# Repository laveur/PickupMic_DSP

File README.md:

# PickupMic_DSP
A Pickup Mic (Piezo) DSP Board

## Info
Based on a STM32F405 MCU, this allows you to connect up to four Piezo (Pickup Mics) To it and do some signal processing on it.

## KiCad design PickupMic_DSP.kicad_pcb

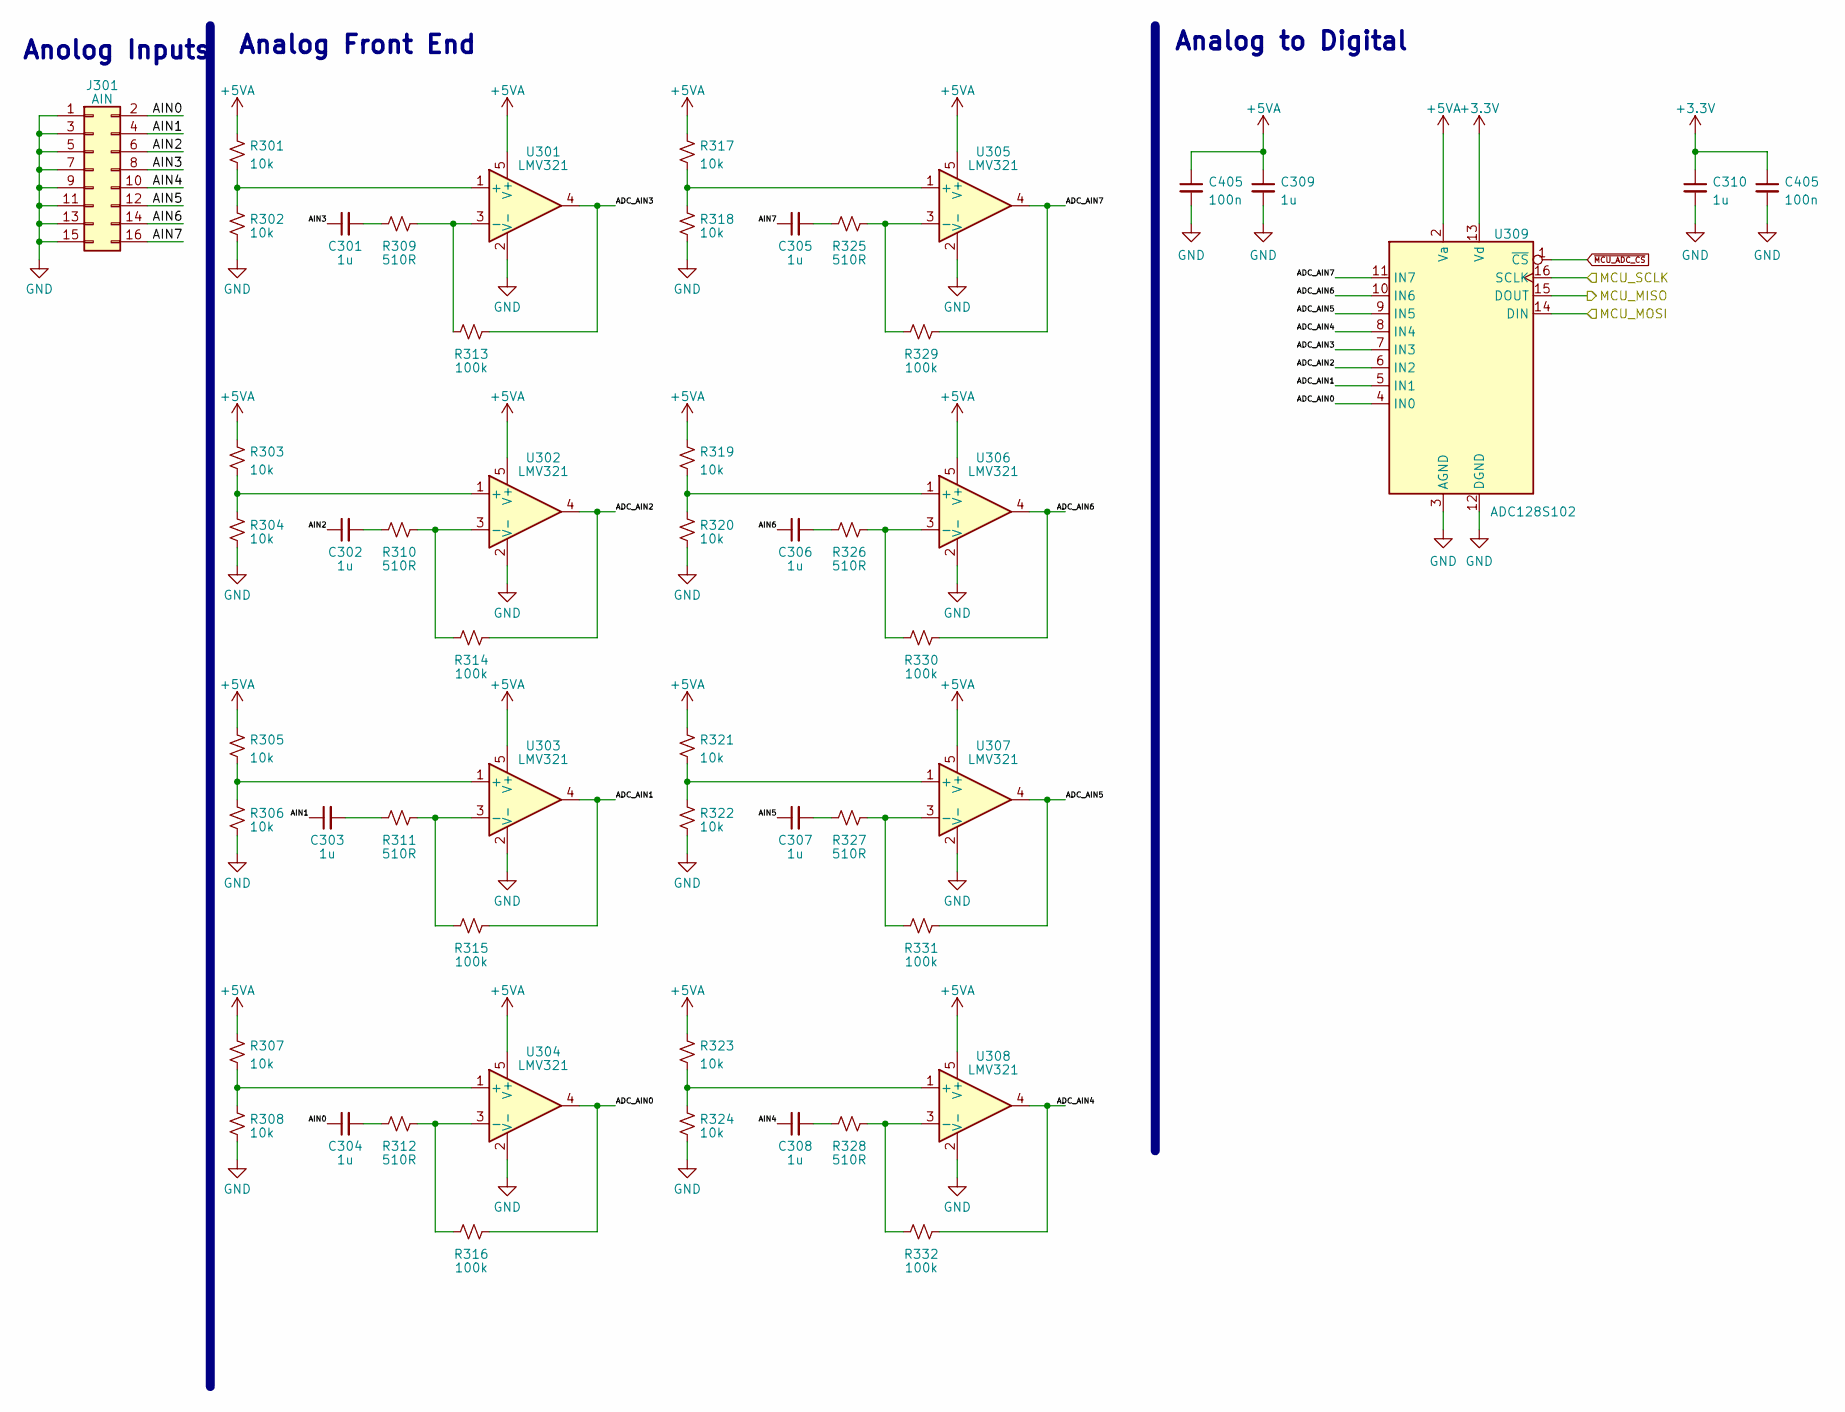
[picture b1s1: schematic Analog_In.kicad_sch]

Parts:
C301, C302, C303, C304, C305, C306, C307, C308, C309, C310: 1u; C_0402_1005Metric; LCSC C52923
C405: 100n; C_0402_1005Metric; LCSC C307331
J301: AIN; PinHeader_2x08_P2.54mm_Vertical
R301, R302, R303, R304, R305, R306, R307, R308, R317, R318, R319, R320, R321, R322, R323, R324: 10k; R_0402_1005Metric; LCSC C144807
R309, R310, R311, R312, R325, R326, R327, R328: 510R; R_0402_1005Metric; LCSC C25123
R313, R314, R315, R316, R329, R330, R331, R332: 100k; R_0402_1005Metric; LCSC C25086
U301, U302, U303, U304, U305, U306, U307, U308: LMV321; SOT-23-5; LCSC C7972
U309: ADC128S102; TSSOP-16_4.4x5mm_P0.65mm; LCSC C179666

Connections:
/Analog In/ADC_AIN0: R316.2, U304.4, U309.4 (IN0)
/Analog In/ADC_AIN1: R315.2, U303.4, U309.5 (IN1)
/Analog In/ADC_AIN2: R314.2, U302.4, U309.6 (IN2)
/Analog In/ADC_AIN4: R332.2, U308.4, U309.8 (IN4)
/Analog In/ADC_AIN5: R331.2, U307.4, U309.9 (IN5)
/Analog In/ADC_AIN6: R330.2, U306.4, U309.10 (IN6)
/Analog In/ADC_AIN7: R329.2, U305.4, U309.11 (IN7)
/Analog In/AIN0: C304.1, J301.2
/Analog In/AIN1: C303.1, J301.4
/Analog In/AIN2: C302.1, J301.6
/Analog In/AIN3: C301.1, J301.8
/Analog In/AIN4: C308.1, J301.10
/Analog In/AIN5: C307.1, J301.12
/Analog In/AIN6: C306.1, J301.14
/Analog In/AIN7: C305.1, J301.16
/Analog In/MCU_MISO: U309.15 (DOUT); also elsewhere on the board
/Analog In/MCU_MOSI: U309.14 (DIN); also elsewhere on the board
/Analog In/MCU_SCLK: U309.16 (SCLK); also elsewhere on the board
unnamed: C301.2, R309.2
unnamed: C302.2, R310.2
unnamed: C303.2, R311.2
unnamed: C304.2, R312.2
unnamed: C305.2, R325.2
unnamed: C306.2, R326.2
unnamed: C307.2, R327.2
unnamed: C308.2, R328.2
unnamed: R301.2, R302.2, U301.1 (+)
unnamed: R303.2, R304.1, U302.1 (+)
unnamed: R310.1, R314.1, U302.3 (-)
unnamed: R305.2, R306.2, U303.1 (+)
unnamed: R311.1, R315.1, U303.3 (-)
unnamed: R307.2, R308.2, U304.1 (+)
unnamed: R312.1, R316.1, U304.3 (-)
unnamed: R317.2, R318.2, U305.1 (+)
unnamed: R325.1, R329.1, U305.3 (-)
unnamed: R319.2, R320.2, U306.1 (+)
unnamed: R326.1, R330.1, U306.3 (-)
unnamed: R321.2, R322.2, U307.1 (+)
unnamed: R327.1, R331.1, U307.3 (-)
unnamed: R323.2, R324.2, U308.1 (+)
unnamed: R328.1, R332.1, U308.3 (-)
~MCU_ADC_CS: U309.1 (~CS); also elsewhere on the board

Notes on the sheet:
Analog Front End
Analog to Digital
Anolog Inputs

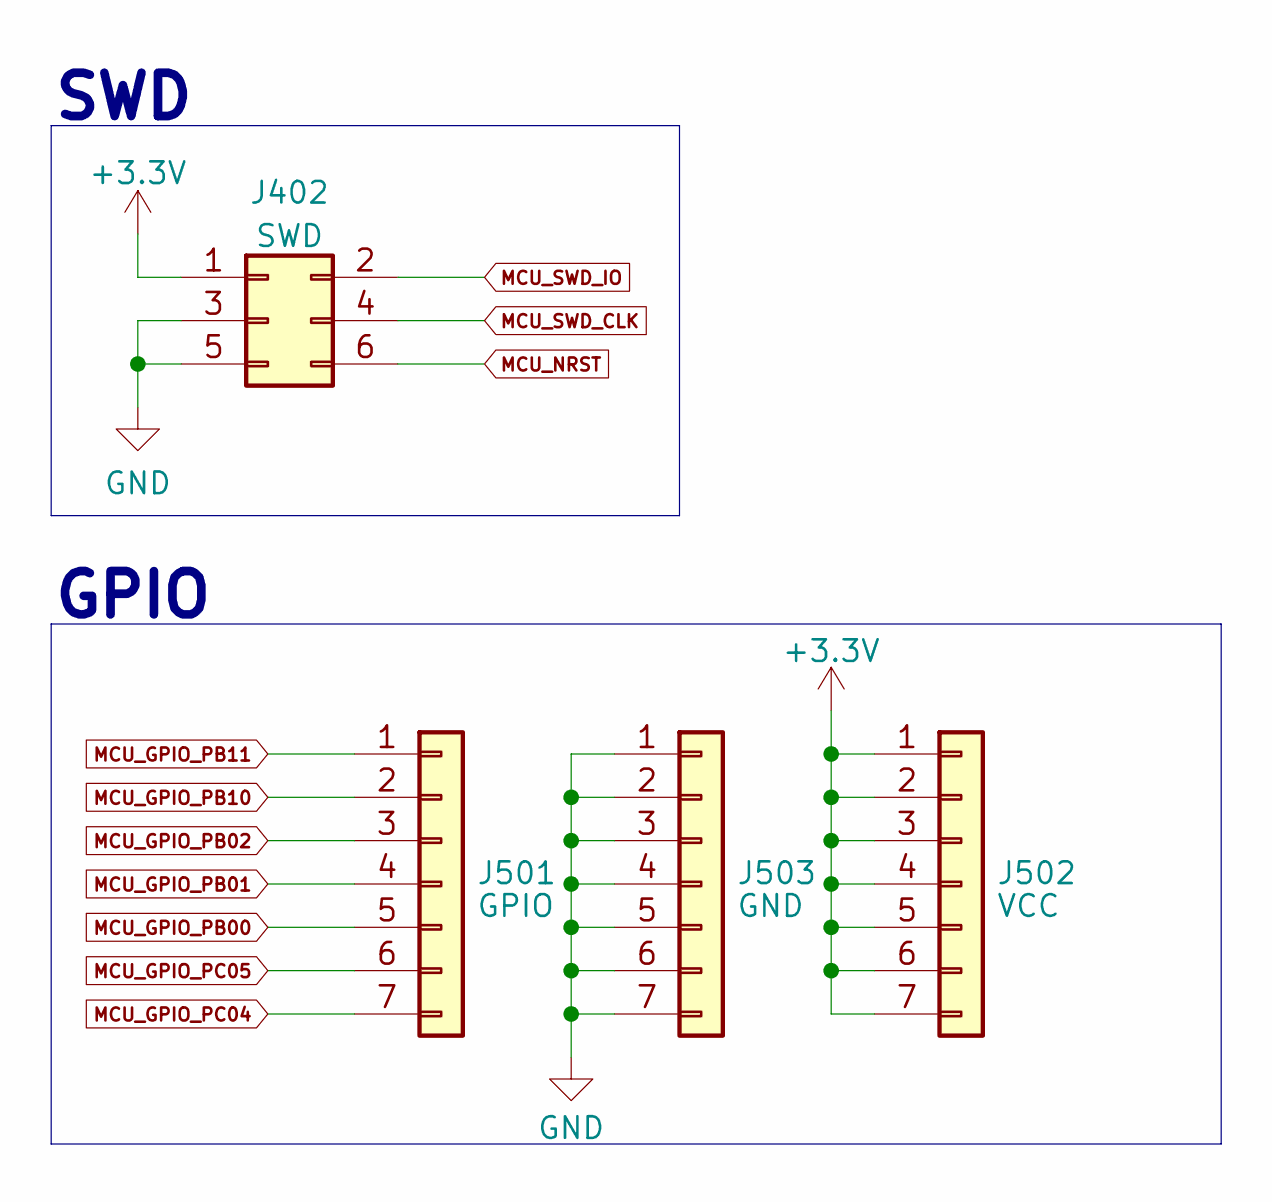
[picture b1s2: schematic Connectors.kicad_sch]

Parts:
J402: SWD; PinHeader_2x03_P2.54mm_Vertical
J501: GPIO; PinHeader_1x07_P2.54mm_Vertical
J502: VCC; PinHeader_1x07_P2.54mm_Vertical
J503: GND; PinHeader_1x07_P2.54mm_Vertical

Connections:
MCU_GPIO_PB00: J501.5; also elsewhere on the board
MCU_GPIO_PB01: J501.4; also elsewhere on the board
MCU_GPIO_PB02: J501.3; also elsewhere on the board
MCU_GPIO_PB10: J501.2; also elsewhere on the board
MCU_GPIO_PB11: J501.1; also elsewhere on the board
MCU_GPIO_PC04: J501.7; also elsewhere on the board
MCU_GPIO_PC05: J501.6; also elsewhere on the board

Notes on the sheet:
SWD
GPIO

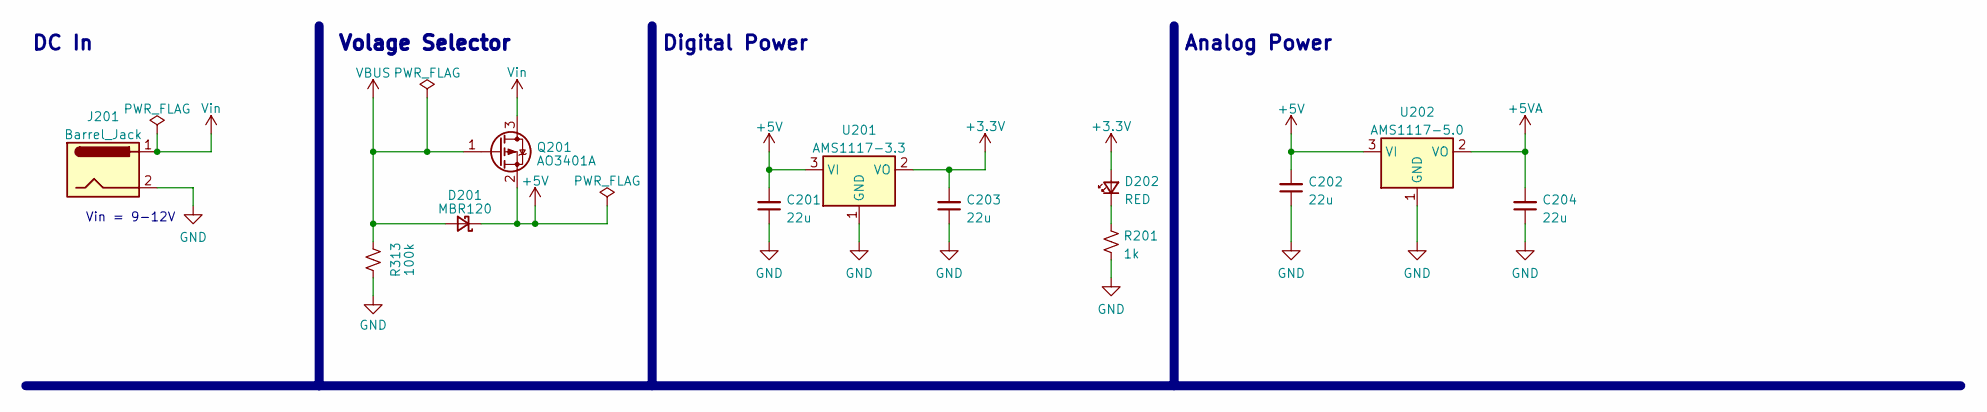
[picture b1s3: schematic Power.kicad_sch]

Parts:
C201, C202, C203, C204: 22u; C_0805_2012Metric; LCSC C45783
D201: MBR120; D_SOD-123; LCSC C130880
D202: RED; LED_0805_2012Metric; LCSC C84256
J201: Barrel_Jack; BarrelJack_Horizontal
Q201: AO3401A; SOT-23
R201: 1k; R_0603_1608Metric; LCSC C105580
R313: 100k; R_0402_1005Metric; LCSC C25086
U201: AMS1117-3.3; SOT-223-3_TabPin2; LCSC C6186
U202: AMS1117-5.0; SOT-223-3_TabPin2; LCSC C6187

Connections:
+5V: C201.2, C202.2, D201.1 (K), Q201.2 (S), U201.3 (VI), U202.3 (VI)
unnamed: D202.1 (K), R201.1
Vin: J201.1, Q201.3 (D)

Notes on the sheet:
Analog Power
Vin = 9-12V
Volage Selector
DC In
Digital Power

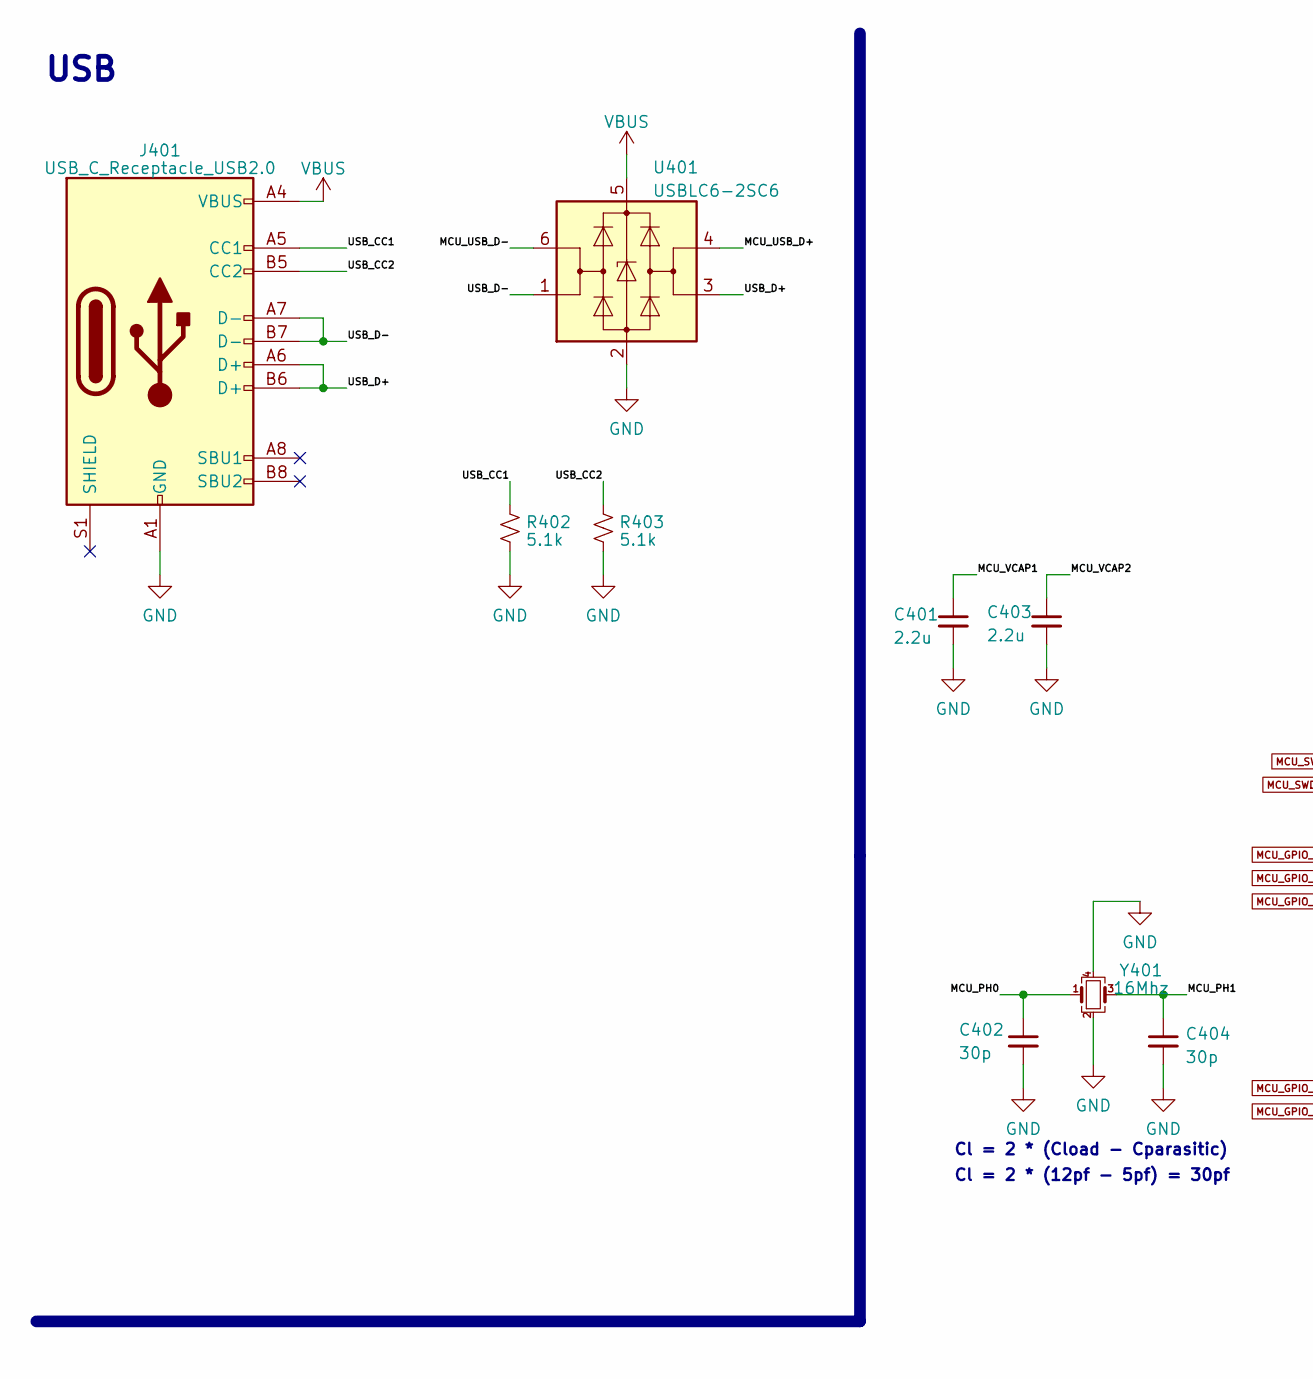
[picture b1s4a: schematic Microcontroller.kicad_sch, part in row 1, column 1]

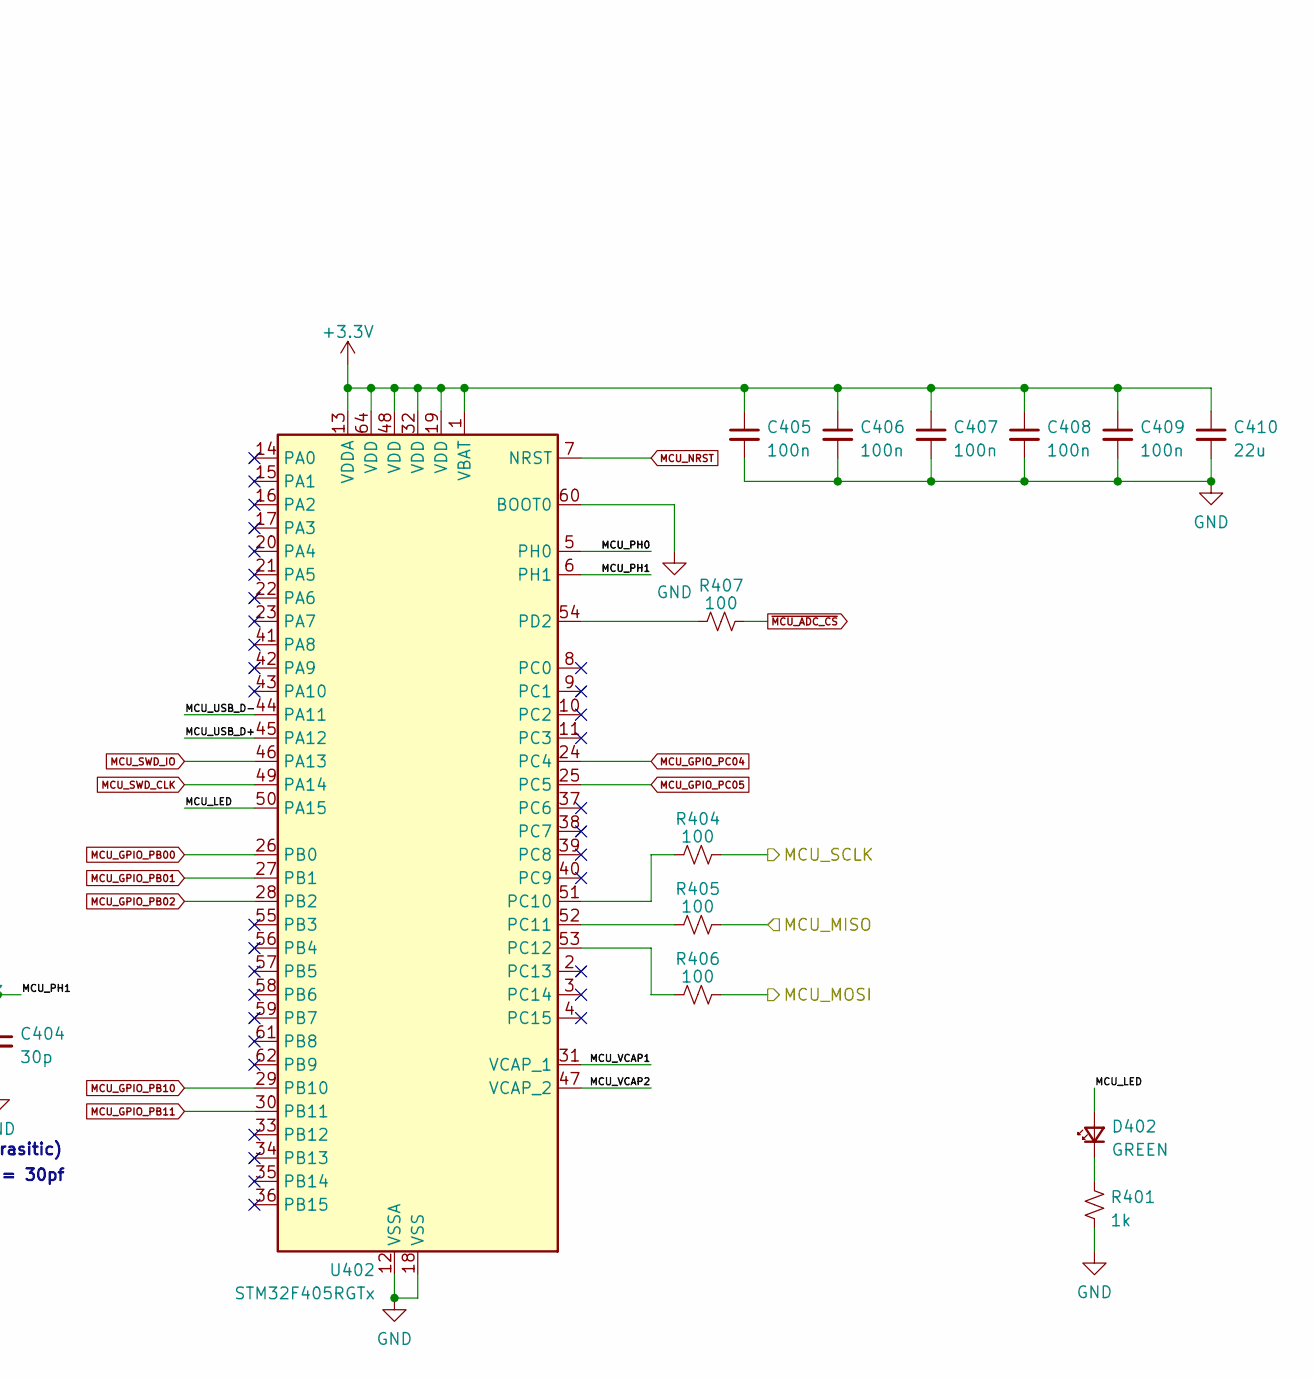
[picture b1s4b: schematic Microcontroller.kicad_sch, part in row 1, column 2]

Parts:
C401, C403: 2.2u; C_0603_1608Metric; LCSC C106853
C402, C404: 30p; C_0603_1608Metric; LCSC C1658
C405, C406, C407, C408, C409: 100n; C_0603_1608Metric; LCSC C105907
C410: 22u; C_0805_2012Metric; LCSC C45783
D402: GREEN; LED_0805_2012Metric; LCSC C142303
J401: USB_C_Receptacle_USB2.0; USB_C_Receptacle_G-Switch_GT-USB-7010ASV; LCSC C2927037
R401: 1k; R_0603_1608Metric; LCSC C105580
R402, R403: 5.1k; R_0603_1608Metric; LCSC C23186
R404, R405, R406, R407: 100; R_0603_1608Metric; LCSC C22775
U401: USBLC6-2SC6; SOT-23-6; LCSC C2827654
U402: STM32F405RGTx; LQFP-64_10x10mm_P0.5mm; LCSC C15742
Y401: 16Mhz; Crystal_SMD_3225-4Pin_3.2x2.5mm; LCSC C133336

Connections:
/Analog In/MCU_MISO: R405.2; also elsewhere on the board
/Analog In/MCU_MOSI: R406.2; also elsewhere on the board
/Analog In/MCU_SCLK: R404.2; also elsewhere on the board
/Microcontroller/MCU_LED: D402.2 (A), U402.50 (PA15)
/Microcontroller/MCU_PH0: C402.1, U402.5 (PH0), Y401.1
/Microcontroller/MCU_PH1: C404.1, U402.6 (PH1), Y401.3
/Microcontroller/MCU_USB_D+: U401.4 (I/O2), U402.45 (PA12)
/Microcontroller/MCU_USB_D-: U401.6 (I/O1), U402.44 (PA11)
/Microcontroller/MCU_VCAP1: C401.1, U402.31 (VCAP_1)
/Microcontroller/MCU_VCAP2: C403.1, U402.47 (VCAP_2)
/Microcontroller/USB_CC1: J401.A5 (CC1), R402.1
/Microcontroller/USB_CC2: J401.B5 (CC2), R403.1
/Microcontroller/USB_D+: J401.A6 (D+), J401.B6 (D+), U401.3 (I/O2)
/Microcontroller/USB_D-: J401.A7 (D-), J401.B7 (D-), U401.1 (I/O1)
MCU_GPIO_PB00: U402.26 (PB0); also elsewhere on the board
MCU_GPIO_PB01: U402.27 (PB1); also elsewhere on the board
MCU_GPIO_PB02: U402.28 (PB2); also elsewhere on the board
MCU_GPIO_PB10: U402.29 (PB10); also elsewhere on the board
MCU_GPIO_PB11: U402.30 (PB11); also elsewhere on the board
MCU_GPIO_PC04: U402.24 (PC4); also elsewhere on the board
MCU_GPIO_PC05: U402.25 (PC5); also elsewhere on the board
MCU_NRST: U402.7 (NRST); also elsewhere on the board
MCU_SWD_CLK: U402.49 (PA14); also elsewhere on the board
MCU_SWD_IO: U402.46 (PA13); also elsewhere on the board
unnamed: D402.1 (K), R401.1
unnamed: R404.1, U402.51 (PC10)
unnamed: R405.1, U402.52 (PC11)
unnamed: R406.1, U402.53 (PC12)
unnamed: R407.1, U402.54 (PD2)
~MCU_ADC_CS: R407.2; also elsewhere on the board

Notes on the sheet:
Cl = 2 * (12pf - 5pf) = 30pf
Cl = 2 * (Cload - Cparasitic)
USB

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
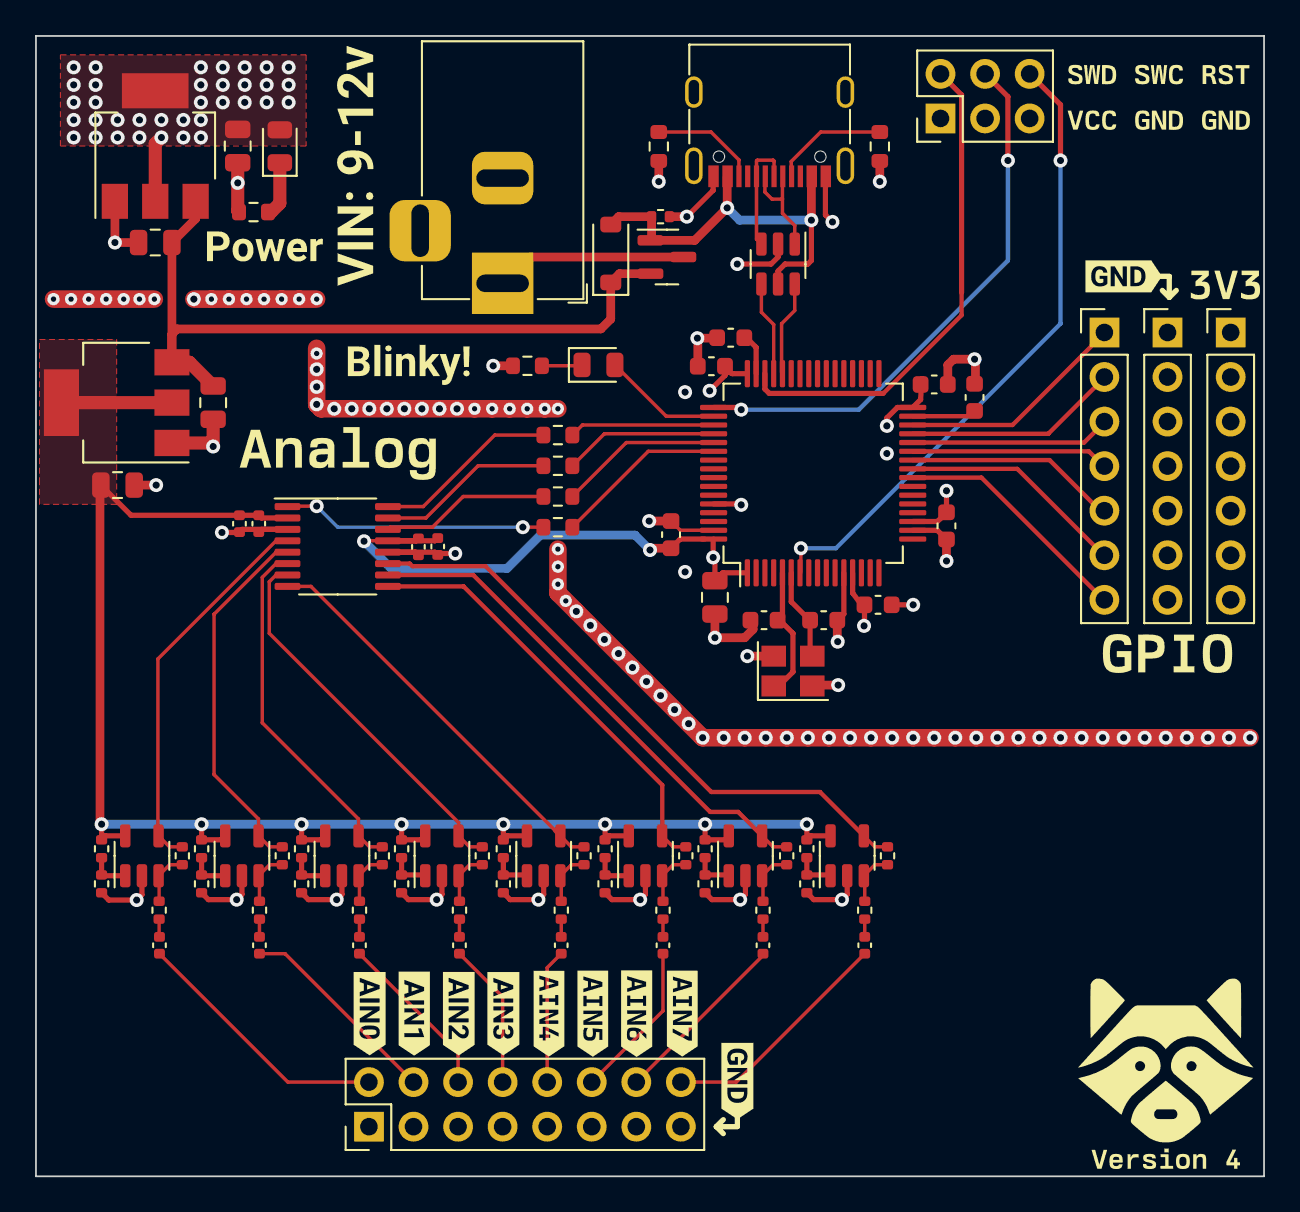
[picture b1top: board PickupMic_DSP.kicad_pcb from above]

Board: 4 copper layers, 70.0 x 65.0 mm, 111 parts (0 on the bottom side), 77 nets.

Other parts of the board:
C311, C312: 100n; C_0402_1005Metric
J504: SWD; PinHeader_2x03_P2.54mm_Vertical
R202: 100k; R_0402_1005Metric
kibuzzard-63BB1A01: G***; kibuzzard-63BB1A01
kibuzzard-63BB1A7D: G***; kibuzzard-63BB1A7D
kibuzzard-63BB1A56: G***; kibuzzard-63BB1A56
kibuzzard-63BB1AB4, kibuzzard-63BB1AB4#2: G***; kibuzzard-63BB1AB4
kibuzzard-63BB1BAF: G***; kibuzzard-63BB1BAF
kibuzzard-63C77ADE: G***; kibuzzard-63C77ADE
kibuzzard-63C77B3E: G***; kibuzzard-63C77B3E
kibuzzard-63CD6EAA: G***; kibuzzard-63CD6EAA
kibuzzard-641D0A5C: G***; kibuzzard-641D0A5C
kibuzzard-641D0A72: G***; kibuzzard-641D0A72
kibuzzard-641D0A85: G***; kibuzzard-641D0A85
kibuzzard-641E03D9: G***; kibuzzard-641E03D9
kibuzzard-6422FB8B: G***; kibuzzard-6422FB8B
kibuzzard-6422FF5E: G***; kibuzzard-6422FF5E
kibuzzard-6423A41B: G***; kibuzzard-6423A41B
kibuzzard-6423A336: G***; kibuzzard-6423A336
kibuzzard-6423A404: G***; kibuzzard-6423A404
kibuzzard-642304B8: G***; kibuzzard-642304B8

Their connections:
MCU_NRST: J504.6; also elsewhere on the board
MCU_SWD_CLK: J504.4; also elsewhere on the board
MCU_SWD_IO: J504.2; also elsewhere on the board

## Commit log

2023-01-08 Initial Commit
    Added Kicad Project files
2023-01-08 Create README.md
    Added a read me file
2023-01-08 Create License
2023-01-08 Small Updates
    * Updated GIT Ignore file to ignore the backups dir.
    * Added missing USB Micro 3D model.
2023-01-23 Switch ADC
    Switched from the ADS1115 to ADS7924 to get faster sampling time.
2023-01-23 Ignore JLC Files
    Ignore my JLCPCB output data.
2023-04-01 Improvements
    Switched ADC to ADC128S.
    Upgraded USB to USB-C
    Improved Analog front end to work with signals better.
